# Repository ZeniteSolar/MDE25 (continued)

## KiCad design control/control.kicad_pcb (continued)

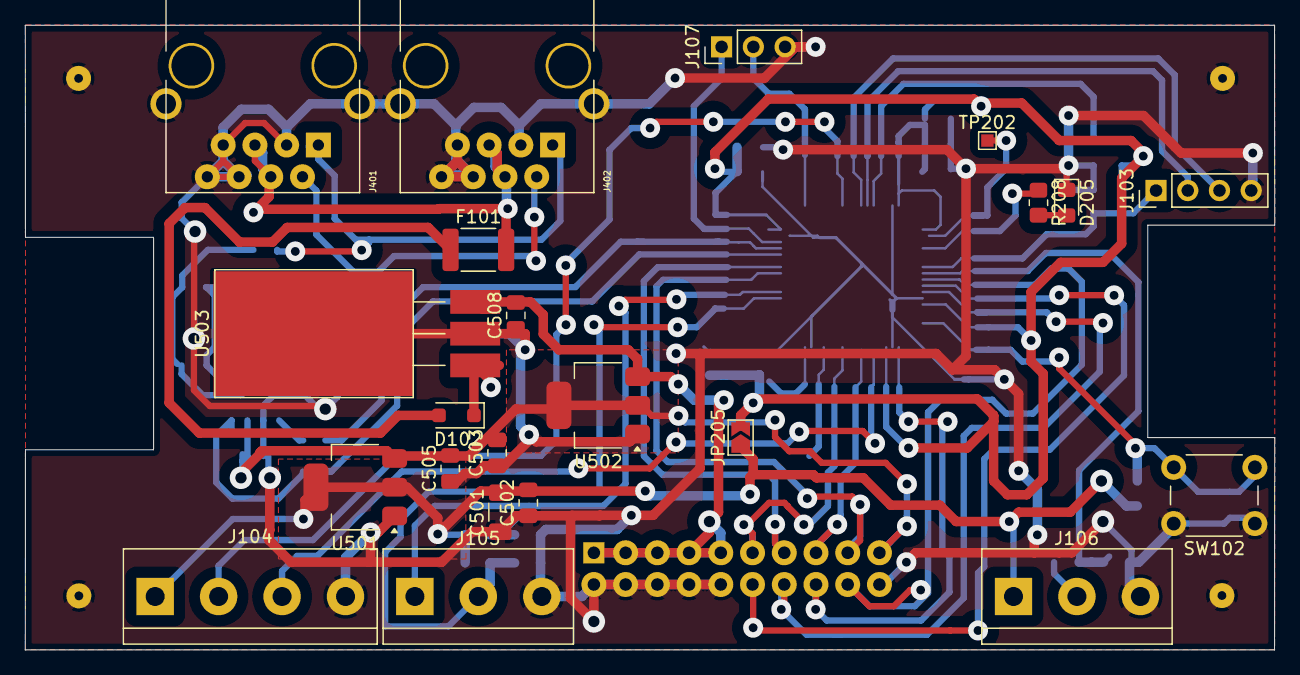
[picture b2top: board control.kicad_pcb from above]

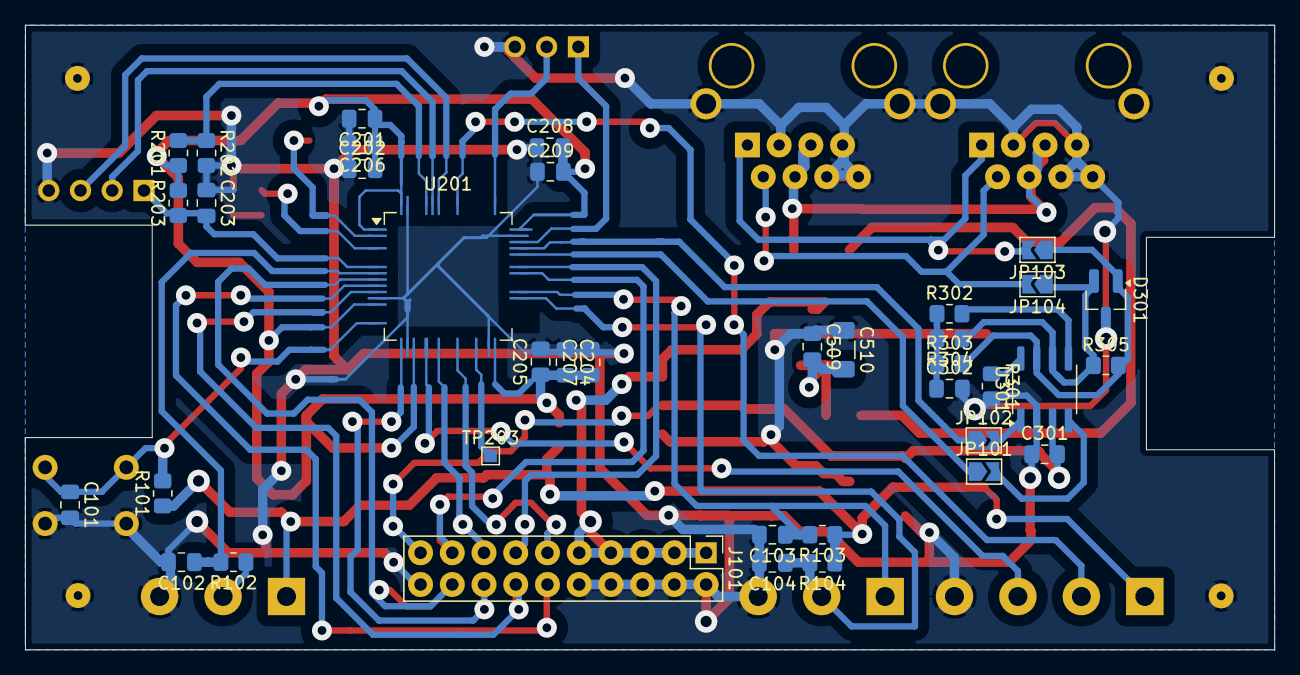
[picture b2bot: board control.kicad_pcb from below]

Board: 2 copper layers, 100.0 x 50.0 mm, 60 parts (38 on the bottom side), 44 nets.

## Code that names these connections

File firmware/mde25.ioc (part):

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Mcu.Name=STM32L431R(B-C)Tx
Mcu.Package=LQFP64
Mcu.UserName=STM32L431RCTx
PA0.GPIOParameters=GPIO_Label
PA0.GPIO_Label=ENCODER_2
PA0.Signal=S_TIM2_CH1
PA1.GPIOParameters=GPIO_Label
PA1.GPIO_Label=ENCODER_1
PA1.Signal=S_TIM2_CH2
PA11.Mode=CAN_Activate
PA11.Signal=CAN1_RX
PA12.Mode=CAN_Activate
PA12.Signal=CAN1_TX
PA13\ (JTMS-SWDIO).GPIOParameters=GPIO_Label
PA13\ (JTMS-SWDIO).GPIO_Label=SWDIO
PA13\ (JTMS-SWDIO).Mode=Serial_Wire
PA13\ (JTMS-SWDIO).Signal=SYS_JTMS-SWDIO
PA14\ (JTCK-SWCLK).GPIOParameters=GPIO_Label
PA14\ (JTCK-SWCLK).GPIO_Label=SWCLK
PA14\ (JTCK-SWCLK).Mode=Serial_Wire
PA14\ (JTCK-SWCLK).Signal=SYS_JTCK-SWCLK
PA2.GPIOParameters=GPIO_Label
PA2.GPIO_Label=ADC_TEMPERATURE
PA2.Signal=ADCx_IN7
PA3.GPIOParameters=GPIO_Label
PA3.GPIO_Label=ADC_INPUT_CURRENT
PA3.Signal=ADCx_IN8
PA7.GPIOParameters=GPIO_Label
PA7.GPIO_Label=PWM_LEFT_LOW
PA7.Mode=PWM Generation1 CH1 CH1N
PA7.Signal=TIM1_CH1N
PA8.GPIOParameters=GPIO_Label
PA8.GPIO_Label=PWM_LEFT_HIGH
PA8.Signal=S_TIM1_CH1
PA9.GPIOParameters=GPIO_Label
PA9.GPIO_Label=PWM_RIGHT_HIGH
PA9.Signal=S_TIM1_CH2
PB0.GPIOParameters=GPIO_Label
PB0.GPIO_Label=PWM_RIGHT_LOW
PB0.Mode=PWM Generation2 CH2 CH2N
PB0.Signal=TIM1_CH2N
PB12.GPIOParameters=GPIO_Label
PB12.GPIO_Label=RED_LED
PB12.Signal=GPIO_Output
PB13.GPIOParameters=GPIO_Label
PB13.GPIO_Label=YELLOW_LED
PB13.Signal=GPIO_Output
PB14.GPIOParameters=GPIO_Label
PB14.GPIO_Label=GREEN_LED
PB14.Signal=GPIO_Output
PB15.GPIOParameters=GPIO_Label
PB15.GPIO_Label=CENTER_SWITCH
PB15.Signal=GPIO_Input
PB6.Mode=Asynchronous
PB6.Signal=USART1_TX
PB7.Mode=Asynchronous
PB7.Signal=USART1_RX
PC0.GPIOParameters=GPIO_Label
PC0.GPIO_Label=ADC_POSITION
PC0.Signal=ADCx_IN1
PC1.GPIOParameters=GPIO_Label
PC1.GPIO_Label=ADC_INPUT_VOLTAGE
PC1.Signal=ADCx_IN2
PC13.GPIOParameters=GPIO_Label
PC13.GPIO_Label=DEBUG_0
PC13.Signal=GPIO_Output
PC14-OSC32_IN\ (PC14).GPIOParameters=GPIO_Label
PC14-OSC32_IN\ (PC14).GPIO_Label=DEBUG_1
PC14-OSC32_IN\ (PC14).Signal=GPIO_Output
PC2.GPIOParameters=GPIO_Label
PC2.GPIO_Label=ADC_OUTPUT_VOLTAGE_P
PC2.Signal=ADCx_IN3
PC3.GPIOParameters=GPIO_Label
PC3.GPIO_Label=ADC_OUTPUT_VOLTAGE_N
PC3.Signal=ADCx_IN4
PC6.GPIOParameters=GPIO_Label
PC6.GPIO_Label=START_SWITCH
PC6.Signal=GPIO_Input
PC7.GPIOParameters=GPIO_Label
PC7.GPIO_Label=END_SWITCH
PC7.Signal=GPIO_Input
RCC.HSE_VALUE=8000000
board=custom

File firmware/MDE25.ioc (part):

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Mcu.Name=STM32L431R(B-C)Tx
Mcu.Package=LQFP64
Mcu.UserName=STM32L431RCTx
PA11.Mode=CAN_Activate
PA11.Signal=CAN1_RX
PA12.Mode=CAN_Activate
PA12.Signal=CAN1_TX
PA13\ (JTMS-SWDIO).Mode=Serial_Wire
PA13\ (JTMS-SWDIO).Signal=SYS_JTMS-SWDIO
PA14\ (JTCK-SWCLK).Mode=Serial_Wire
PA14\ (JTCK-SWCLK).Signal=SYS_JTCK-SWCLK
PA2.GPIOParameters=GPIO_Label
PA2.GPIO_Label=USER_BUTTON
PA2.Signal=GPXTI2
PA3.Signal=ADCx_IN8
PA7.Mode=PWM Generation1 CH1 CH1N
PA7.Signal=TIM1_CH1N
PA8.Signal=S_TIM1_CH1
PA9.Signal=S_TIM1_CH2
PB0.Mode=PWM Generation2 CH2 CH2N
PB0.Signal=TIM1_CH2N
PB10.GPIOParameters=GPIO_Label
PB10.GPIO_Label=USER_DEBUG_0
PB10.Signal=GPIO_Output
PB6.GPIOParameters=GPIO_PuPd
PB6.GPIO_PuPd=GPIO_PULLUP
PB6.Mode=Asynchronous
PB6.Signal=USART1_TX
PB7.GPIOParameters=GPIO_PuPd
PB7.GPIO_PuPd=GPIO_PULLUP
PB7.Mode=Asynchronous
PB7.Signal=USART1_RX
PC0.Signal=ADCx_IN1
PC1.GPIOParameters=GPIO_Label
PC1.GPIO_Label=INPUT_VOLTAGE
PC1.Signal=ADCx_IN2
PC13.GPIOParameters=GPIO_Label
PC13.GPIO_Label=USER_DEBUG_1
PC13.Signal=GPIO_Output
PC15-OSC32_OUT\ (PC15).GPIOParameters=GPIO_Label
PC15-OSC32_OUT\ (PC15).GPIO_Label=USER_LED_RED
PC15-OSC32_OUT\ (PC15).Signal=GPIO_Output
PC2.GPIOParameters=GPIO_Label
PC2.GPIO_Label=OUTPUT_VOLTAGE_P
PC2.Signal=ADCx_IN3
PC3.GPIOParameters=GPIO_Label
PC3.GPIO_Label=OUTPUT_VOLTAGE_N
PC3.Signal=ADCx_IN4
RCC.HSE_VALUE=8000000
RCC.SYSCLKFreq_VALUE=80000000
RCC.SYSCLKSource=RCC_SYSCLKSOURCE_PLLCLK
board=custom

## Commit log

2025-06-27 Update gitignore
2025-06-27 Create basic pin configuration using cubeMX
2025-06-27 Route power board layout
2025-06-27 Route control board layout
2025-06-29 Add UV fab files
2025-07-14 Add firmware
2025-07-27 Add first complete operational firmware
2025-07-27 Move hardware projects to subfolder
2025-07-27 Organize schematics per domain
2025-07-27 Add schematic hardware plots
2025-07-28 Docs: Add basic docs
2025-07-28 Add base relatory
2025-07-28 Adjust titles
2025-07-28 Fix figures names
2025-07-28 Fix list style
2025-07-28 Remove unicode
2025-07-28 Move docs to README
2025-07-28 Add project logo
2025-08-14 Modify max output voltage
2025-09-02 Handle can errors
2025-09-02 Fix compilation
2025-09-06 Add watchdog
2025-09-09 Update cubeMX version
2025-09-09 Add independent watchdog
2025-09-09 Add uart pull-ups
2025-09-09 Add can automatic bus off
